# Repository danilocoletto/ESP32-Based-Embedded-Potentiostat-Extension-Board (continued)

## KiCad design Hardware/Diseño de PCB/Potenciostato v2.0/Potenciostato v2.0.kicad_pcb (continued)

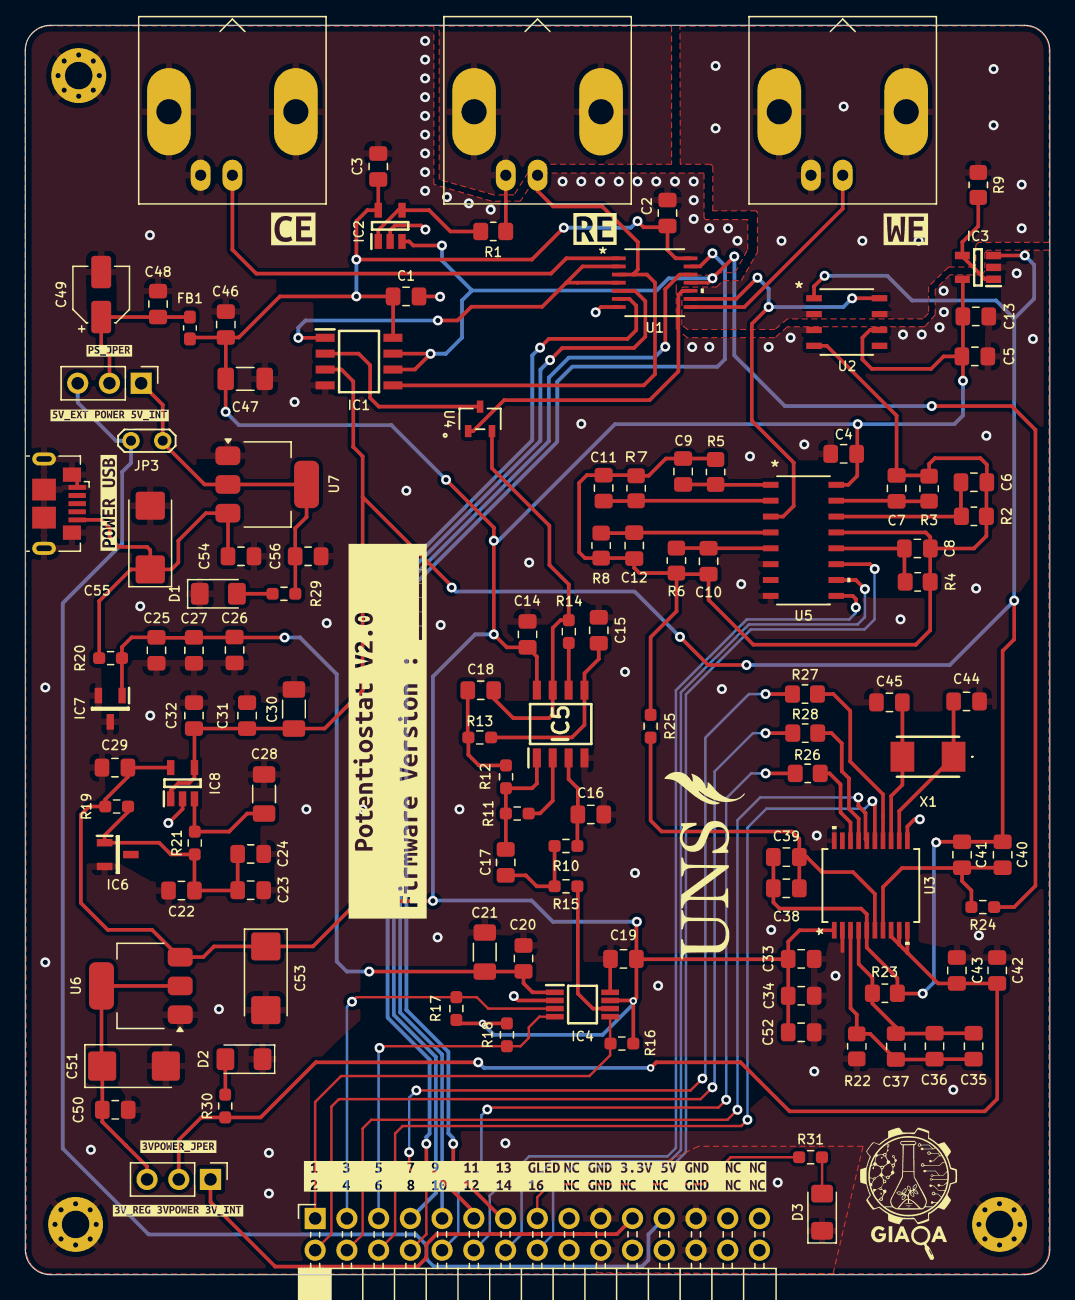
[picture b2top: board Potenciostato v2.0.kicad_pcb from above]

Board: 2 copper layers, 82.0 x 100.0 mm, 129 parts (0 on the bottom side), 70 nets.

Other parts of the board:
kibuzzard-68ED1B67: G***; kibuzzard-68ED1B67
kibuzzard-68ED1EA7: G***; kibuzzard-68ED1EA7
kibuzzard-68ED1F3F: G***; kibuzzard-68ED1F3F
kibuzzard-68ED1F9A: G***; kibuzzard-68ED1F9A
kibuzzard-68ED1F51: G***; kibuzzard-68ED1F51
kibuzzard-68ED337E: G***; kibuzzard-68ED337E
kibuzzard-68ED3374: G***; kibuzzard-68ED3374
kibuzzard-68ED3386: G***; kibuzzard-68ED3386
kibuzzard-68ED3787: G***; kibuzzard-68ED3787
kibuzzard-68F13228: G***; kibuzzard-68F13228
kibuzzard-68F13266: G***; kibuzzard-68F13266

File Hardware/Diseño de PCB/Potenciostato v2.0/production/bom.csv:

Designator,Footprint,Quantity,Value,LCSC Part #
"C1, C13, C14, C19, C20, C23, C26, C29, C3, C34, C36, C38, C4, C40, C42, C48, C5, C50, C52, C54, C56",0805,21,100n,
C10,0805,1,2p,
C11,0805,1,0.2p,
C12,0805,1,0.1p,
C15,0805,1,68p,
C16,0805,1,160p,
"C17, C18",0805,2,180p,
"C2, C46",0805,2,10n,
"C21, C28",1206,2,1u,
"C22, C25, C32, C35",0805,4,47u,
"C24, C27, C37, C39, C41",0805,5,100p,
C30,1206,1,100u,
C31,0805,1,0.1u,
"C33, C43",0805,2,10u,
"C44, C45",0805,2,18p,
C47,1206,1,2.2n,
C49,CP_Elec_4x5.4,1,10u,
"C51, C53, C55",CP_EIA-6032-20_AVX-F_Pad2.25x2.35mm_HandSolder,3,10u,
C6,0805,1,56n,
C7,0805,1,2n,
C8,0805,1,200p,
C9,0805,1,20p,
D1,1206,1,Red,
D2,1206,1,Yellow,
D3,1206,1,Green,
FB1,0603,1,FerriteBead_Small,
IC1,SOIC127P600X175_LMP7702,1,LMP7702MAX_NOPB,
"IC2, IC3",SOT95P280X145_LMP7701,2,LMP7701MFX_NOPB,
IC4,SOP65P490X110_MAX5217,1,MAX5217GUA+,
IC5,SOIC127P600X175_MAX4477,1,MAX4477ASA+,
IC6,SOT95P237X112_LM40402_5,1,LM4040AIM3X-2.5_NOPB,
IC7,SOT95P237X112_LM4040A5,1,LM4040A50IDBZR,
IC8,SOT95P280X145_OPA354,1,OPA354AIDBVT,
"J1, J3, J5",BNC_Amphenol_B6252HB-NPP3G-50_Horizontal,3,Conn_Coaxial,
J2,PinSocket_2x15_P2.54mm_Horizontal,1,Conn_02x15_Odd_Even,
J7,USB_Micro-B_GCT_USB3076-30-A,1,USB_B_Micro,
JP3,TestPoint_2Pads_Pitch2.54mm_Drill0.8mm,1,Jumper_2_Open,
"R1, R2, R26, R27, R28, R9",0805,6,100,
"R10, R15",0603,2,18.7k,
"R11, R14, R19, R20",0603,4,1k,
"R12, R13",0603,2,25.5k,
"R16, R17, R18",0603,3,4.7k,
R21,0603,1,10k,
"R22, R23",0805,2,49.9,
"R24, R25",0603,2,300,
"R29, R30, R31",0603,3,470,
R3,0805,1,3k,
R4,0805,1,30k,
R5,0805,1,300k,
R6,0805,1,3M,
R7,0805,1,30M,
R8,0805,1,100M,
U1,MAX4737,1,MAX4737EUD+,
U2,M08ALMP7721_,1,LMP7721MA/NOPB,
U3,DB20_ADS1255,1,ADS1255IDBR,
U4,SOT23_5491,1,MAX5491LA01000+T,
U5,MAX4617,1,MAX4617CSE+,
U6,SOT-223-3_TabPin2,1,AMS1117-3.3,
U7,SOT-223-3_TabPin2,1,AMS1117-5.0,
X1,CRYSTAL_8,1,XTAL8MHZ,

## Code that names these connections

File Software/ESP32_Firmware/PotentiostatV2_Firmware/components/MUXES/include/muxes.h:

/*******************************************************************************
 * @file        muxes.h
 * @brief       C Library to control  Digital Muxes MAX4737EUD and MAX4617CSE+
 * @details     This file implements the functionalities of the Muxes
 * @version     1.0
 * @author      Ing. Danilo Coletto Gallego
 * @date        11.12.2025
 * @copyright   (c) 2025  Universidad Nacional del Sur - CONICET
 * @see         
******************************************************************************** 

MIT License
*/

#include "general.h"

#define     CONNECTED           1
#define     DISCONNECTED        0

// --- PINOUT MAX4617 FOR ESP32 ---

#define MAX4617_SEL_A       GPIO_NUM_27
#define MAX4617_SEL_B       GPIO_NUM_26
#define MAX4617_SEL_C       GPIO_NUM_25

// --- PINOUT MAX4737 FOR ESP32 ---

#define MAX4737_CR_SHORT_EN     GPIO_NUM_14
#define MAX4737_RE_FB_EN        GPIO_NUM_33
#define MAX4737_WE_EN           GPIO_NUM_13
#define MAX4737_CE_EN           GPIO_NUM_15

// --- GAIN VALUES ---

#define NO_GAIN				    0
#define GAIN1_100			    1
#define GAIN2_3K			    2
#define GAIN3_30K			    3
#define GAIN4_300K			    4
#define GAIN5_3M			    5
#define GAIN6_30M			    6
#define GAIN7_100M			    7


void MAX4617_Config_Pins    (void);
void MAX4617_Set_Gain       (int gain);
int MAX4617_get_gain        (void);


void MAX4737_Config_Pins    (void);

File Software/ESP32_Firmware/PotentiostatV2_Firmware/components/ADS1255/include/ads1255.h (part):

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#define GEN_CLOCK

#ifdef GEN_CLOCK
  #define ADS1255_CLOCK_PIN     GPIO_NUM_16 
#endif

#define ADS1255_DOUT_MISO       GPIO_NUM_19
#define ADS1255_DIN_MOSI        GPIO_NUM_23
#define ADS1255_SCLK            GPIO_NUM_18
#define ADS1255_CS              GPIO_NUM_5
#define ADS1255_DRDY            GPIO_NUM_4

// ADS1256 Register
#define ADS125X_REG_STATUS      0x00
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
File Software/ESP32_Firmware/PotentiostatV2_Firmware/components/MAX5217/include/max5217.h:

/*******************************************************************************
 * @file        max5217.h
 * @brief       C Header Library for MAX5217 Digital to Analog Converter
 * @details     This file implements the functionalities of the DAC.
 * @version     1.0
 * @author      Ing. Danilo Coletto Gallego
 * @date        04.12.2025
 * @copyright   (c) 2025  Universidad Nacional del Sur - CONICET
 * @see         
******************************************************************************** 
 */

#ifndef MAX5217_H
#define	MAX5217_H

#include <stdio.h>
#include "driver/i2c_master.h"
#include "general.h"


// Definiciones de pines (Ajústalo a tu placa)
#define MAX_5217_NAUX             GPIO_NUM_32
#define MAX_5217_SCL              GPIO_NUM_22
#define MAX_5217_SDA              GPIO_NUM_21
#define I2C_MASTER_FREQ_HZ        400000    // 100kHz o 400kHz

// DATOS DEL DAC
#define DAC1_DEVICE_ID 	            0x1C
#define DAC_REF_5V 		            5000
#define DAC_REF_2_5V 	            2500
#define MAX_VALUE_DAC	            65500


// COMANDOS DEL DAC
#define MAX5217_CMD_NO_OP 			0x00
#define MAX5217_CMD_CODE_LOAD 		0x01
#define MAX5217_CMD_CODE			0x02
#define MAX5217_CMD_LOAD			0x03
#define MAX5217_CMD_USER_CONFIG 	0x08
#define MAX5217_CMD_SW_RESET 		0x09
#define MAX5217_CMD_SW_CLEAR		0x10




/*********Internal Functions for ADS1255*********/
void                        I2C_Scanner              (i2c_master_bus_handle_t bus_handle);

/**************Functions for ADS1255************/

i2c_master_dev_handle_t     MAX5217_Setup_DAC        (uint8_t devID);
void                        MAX5217_Write_DAC_MV     (i2c_master_dev_handle_t dac_handle, float mvolt_value);
void                        MAX5217_Clear_DAC        (i2c_master_dev_handle_t dac_handle);

/*********HAL Layer Functions for ADS1255*********/

void        MAX5217_DAC_Setup_HAL       (void);
int         MAX5217_DAC_WRITE_HAL_MV    (float millivoltage);
void        MAX5217_DAC_CLEAR_HAL       (void);

#endif	/* MAX5217_H */

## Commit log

2025-10-19 Commit Inicial del Repositorio. Creacion de las Carpetas. Hardware Finalizado. No hay Software desarrollado.
2025-12-17 Big commit. Hardware was already ready. Board arrived. Hardware testing phase and software development is ongoing, some hardware issues were detected and noted down in the KiCad project for future ve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
2025-12-17 Hardware modifications. More notes added to the KiCad project related to hardware issues found during testing. USB Power and ground inverted corrected in design and PCB. MAX4477 replaced by OPA2320 i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
2025-12-17 ADC, DAC, MUXES and GPIO libraries operational and working. There is still work to do and further commplementary functions to implement but the basics are ready and functional. Is necessary to implem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
2025-12-17 README updated
2025-12-17 New README update
2025-12-17 Another README Update.md
2025-12-22 Further documentation and notes on the schematic. Software updates: In MAX4617, corrections in write function, more robust code verification to prevent overflows. In MUX, correction to MAX4617 gain c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
2026-02-06 BIG COMMIT. Big delayed commit. Huge ammount of changes in most dependences: - Timer library renamed to General where there are functions for diverse neccesities. - ADC library, huge changes: Lots of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
2026-02-06 Updated Hardware project. There is no changes recorded but to keep a clean track of the repository.
2026-02-06 ADS1255 datasheet added. ADS1255 example libraries for STM32 also added.
2026-02-25 This commit updates the firmware greatly. FSM machine for the main system has been implemented containing communication with the Python Software Interface. Integration with this interface has begin. 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
2026-02-25 No changes in hardware. New
2026-02-25 changes in gitignore
2026-02-26 Firmware Update: Further communications improvements between firmware and Interface, more commands added. Standarization of commands in general.h, standarization of experiments and experiments header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
2026-02-27 Hardware: Hardware Corrections in Potentiostat, small but important ones (WE electrode, Normal Open connection for electric disconnection in schematic and PCB. DAC I2C pull up resistors connected to 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
2026-03-03 Se resolvieron multiples incovenientes criticos en la interfaz y el backend. Principalmente, problemas que ralentizaban la lecturas de las muestras asociados con las graficas. Se agregaron tasas de r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
2026-03-03 Smalls fixes and optimizations to backend. Polishing code.
2026-03-03 Last big problems solved with interface and backend. Added a QThread for scanner to prevent UI from freezing. Added file and parameters check before loading configuration and more small fixes. Added 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
2026-03-04 Interfaz actualizada. Implementacion del viewer para visualizar graficas, optimizacion final con filtros sobre los datos. Funcionalidad al 100%. Pequeños fixes por el camino, version estable y practi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
2026-03-05 Physical Disconnection Device Detection added to UI. Preconditioning treatment implemented in firmware and small fixes related to it. Other smalls fixes in UI related to new featured implemented. UI 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
2026-03-09 CPE fully incorporated and implemented in firmwared and software. Data display updated and upgrated with auto scale selector. 3D design files for case added.
2026-03-09 readme update
2026-03-12 GPIO library deleted and funtionalities absorbed by general library. Changes in order libraries to rearrange this modification. Images and captures added.
2026-03-13 DPV technique added. Firmware and Interface Software Updated to v1.1. Data storage format updated.
2026-03-13 Interface v1.1 rebuilded.
2026-03-27 ESP32 Board 5V pinout correction
2026-03-27 large .zip deleted
